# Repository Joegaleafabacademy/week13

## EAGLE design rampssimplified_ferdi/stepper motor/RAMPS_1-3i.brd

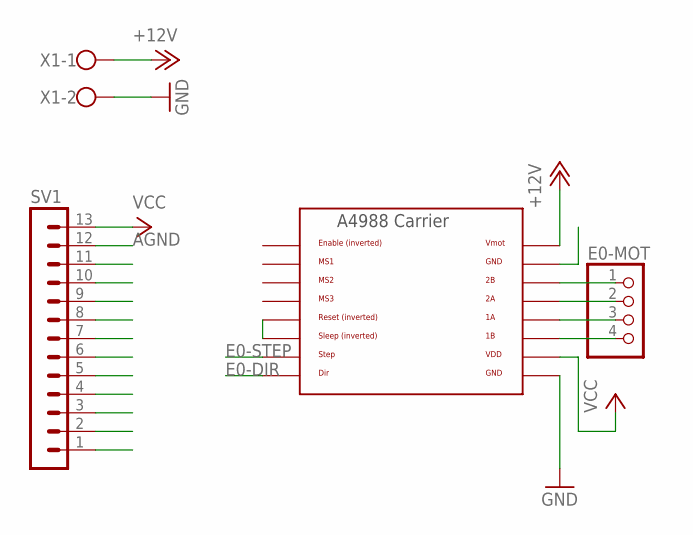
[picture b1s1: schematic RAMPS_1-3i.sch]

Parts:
E0-MOT: PINHD-1X4; 1X04
SV1: MA13-1
U$4: A4988BREAKOUT
X1: W237-102

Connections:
+12V: U$4.VMOT, X1.1
AGND: SV1.12, U$4.GND
E0-DIR: SV1.1, U$4.DIR
E0-STEP: SV1.2, U$4.STEP
GND: U$4.GND@0 (GND), X1.2
unnamed: E0-MOT.1, U$4.2B
unnamed: E0-MOT.2, U$4.2A
unnamed: U$4.RST, U$4.SLP (SLEEP)
unnamed: E0-MOT.3, U$4.1A
unnamed: E0-MOT.4, U$4.1B
VCC: SV1.13, U$4.VDD

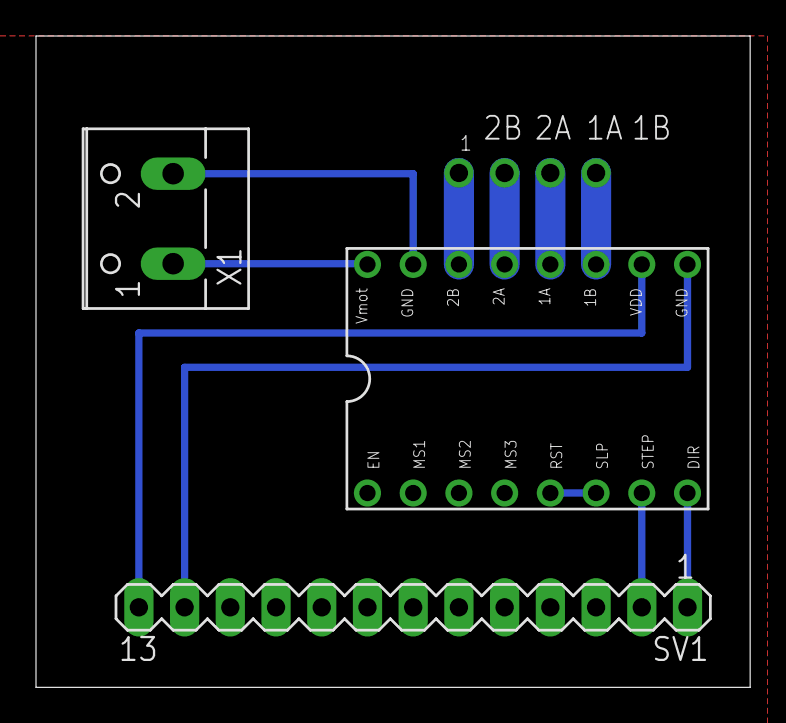
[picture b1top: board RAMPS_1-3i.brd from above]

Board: 2 copper layers, 39.7 x 36.2 mm, 4 parts (0 on the bottom side), 11 nets.

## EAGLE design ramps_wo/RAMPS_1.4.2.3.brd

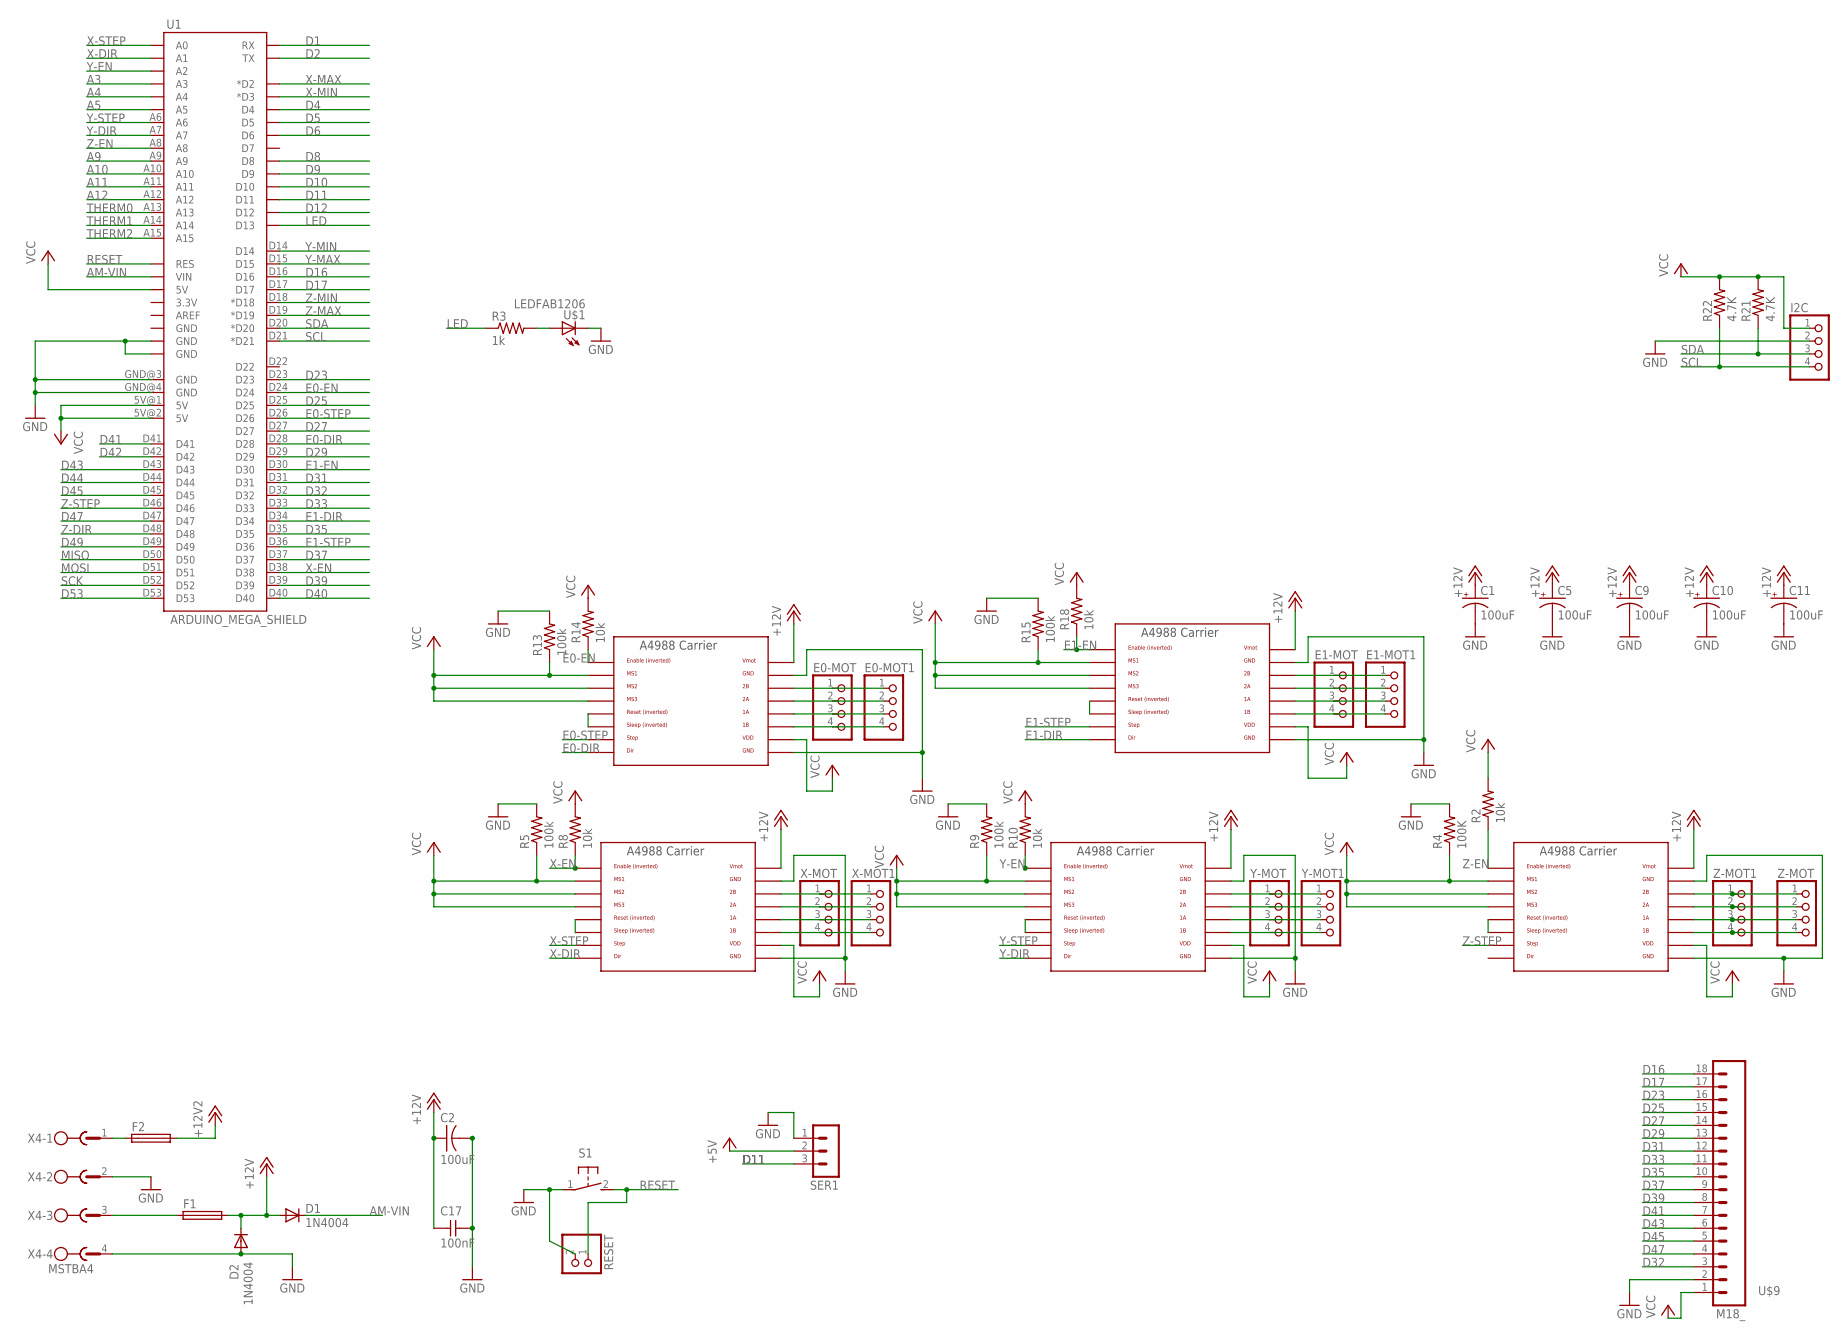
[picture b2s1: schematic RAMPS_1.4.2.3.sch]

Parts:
C1, C5, C9, C10, C11: 100uF; 153CLV-0605
C2: 100uF; C1206FAB
C17: 100nF; C1206FAB
D1, D2: 1N4004; DO41-10
E0-MOT, E0-MOT1, E1-MOT, E1-MOT1: PINHD-1X4; 1X04
F1, F2: FUSE_MCCQ-122
I2C: PINHD-1X4; 1X04
R2, R8, R10, R14, R18: 10k; R1206FAB
R3: 1k; R1206FAB
R4: 100K; R1206FAB
R5, R9, R13, R15: 100k; R1206FAB
R21, R22: 4.7K; R0805
RESET: PINHD-2
S1: 31-XX; B3F-31XX
SER1: 3PIN-HEADER
U1: ARDUINO_MEGA_SHIELD
U$1: LEDFAB1206; LED1206FAB
U$4, U$5, U$6, U$7, U$8: A4988BREAKOUT
U$9: M18_; 1X18
X4: MSTBA4
X-MOT, X-MOT1: PINHD-1X4; 1X04
Y-MOT, Y-MOT1: PINHD-1X4; 1X04
Z-MOT, Z-MOT1: PINHD-1X4; 1X04

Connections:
+5V: SER1.2
+12V: C1.+, C2.1, C5.+, C9.+, C10.+, C11.+, C17.1, D1.A, D2.C, F1.2-1 (2), F1.2-2 (2), U$4.VMOT, U$5.VMOT, U$6.VMOT, U$7.VMOT, U$8.VMOT
+12V2: F2.2-1 (2), F2.2-2 (2)
A3: U1.A3
A4: U1.A4
A5: U1.A5
A9: U1.A9
A10: U1.A10
A11: U1.A11
A12: U1.A12
AM-VIN: D1.C, U1.VIN
D1: U1.RX
D2: U1.TX
D4: U1.D4
D5: U1.D5
D6: U1.D6
D8: U1.D8
D9: U1.D9
D10: U1.D10
D11: SER1.3, U1.D11
D12: U1.D12
D16: U1.D16, U$9.18
D17: U1.D17, U$9.17
D23: U1.D23, U$9.16
D25: U1.D25, U$9.15
D27: U1.D27, U$9.14
D29: U1.D29, U$9.13
D31: U1.D31, U$9.12
D32: U1.D32, U$9.3
D33: U1.D33, U$9.11
D35: U1.D35, U$9.10
D37: U1.D37, U$9.9
D39: U1.D39, U$9.8
D40: U1.D40
D41: U1.D41, U$9.7
D42: U1.D42
D43: U1.D43, U$9.6
D44: U1.D44
D45: U1.D45, U$9.5
D47: U1.D47, U$9.4
D49: U1.D49
D53: U1.D53
E0-DIR: U1.D28, U$4.DIR
E0-EN: R14.1, U1.D24, U$4.EN
E0-STEP: U1.D26, U$4.STEP
E1-DIR: U1.D34, U$5.DIR
E1-EN: R18.1, U1.D30, U$5.EN
E1-STEP: U1.D36, U$5.STEP
GND: C1.-, C2.2, C5.-, C9.-, C10.-, C11.-, C17.2, D2.A, I2C.2, R4.2, R5.2, R9.2, R13.2, R15.2, RESET.2, S1.1, SER1.1, U1.GND@0 (GND), U1.GND@1 (GND), U1.GND@3 (GND), U1.GND@4 (GND), U$1.2 (C), U$4.GND, U$4.GND@0 (GND), U$5.GND, U$5.GND@0 (GND), U$6.GND, U$6.GND@0 (GND), U$7.GND, U$7.GND@0 (GND), U$8.GND, U$8.GND@0 (GND), U$9.2, X4.2, X4.4
LED: R3.1, U1.D13
MISO: U1.D50
MOSI: U1.D51
unnamed: E0-MOT.1, E0-MOT1.1, U$4.2B
unnamed: E0-MOT.2, E0-MOT1.2, U$4.2A
unnamed: U$4.RST, U$4.SLP (SLEEP)
unnamed: E0-MOT.3, E0-MOT1.3, U$4.1A
unnamed: E0-MOT.4, E0-MOT1.4, U$4.1B
unnamed: E1-MOT.1, E1-MOT1.1, U$5.2B
unnamed: E1-MOT.2, E1-MOT1.2, U$5.2A
unnamed: E1-MOT.3, E1-MOT1.3, U$5.1A
unnamed: E1-MOT.4, E1-MOT1.4, U$5.1B
unnamed: U$6.RST, U$6.SLP (SLEEP)
unnamed: U$6.2B, X-MOT.1, X-MOT1.1
unnamed: U$6.2A, X-MOT.2, X-MOT1.2
unnamed: U$7.RST, U$7.SLP (SLEEP)
unnamed: U$5.RST, U$5.SLP (SLEEP)
unnamed: U$6.1A, X-MOT.3, X-MOT1.3
unnamed: U$6.1B, X-MOT.4, X-MOT1.4
unnamed: U$7.2B, Y-MOT.1, Y-MOT1.1
unnamed: U$7.2A, Y-MOT.2, Y-MOT1.2
unnamed: U$7.1A, Y-MOT.3, Y-MOT1.3
unnamed: U$7.1B, Y-MOT.4, Y-MOT1.4
unnamed: U$8.RST, U$8.SLP (SLEEP)
unnamed: U$8.2B, Z-MOT.1, Z-MOT1.1
unnamed: U$8.2A, Z-MOT.2, Z-MOT1.2
unnamed: U$8.1A, Z-MOT.3, Z-MOT1.3
unnamed: U$8.1B, Z-MOT.4, Z-MOT1.4
unnamed: R3.2, U$1.1 (A)
unnamed: F2.1-1 (1), F2.1-2 (1), X4.1
unnamed: F1.1-1 (1), F1.1-2 (1), X4.3
RESET: RESET.1, S1.2 (S), U1.RES
SCK: U1.D52
SCL: I2C.4, R22.1, U1.D21 (*D21)
SDA: I2C.3, R21.1, U1.D20 (*D20)
THERM0: U1.A13
THERM1: U1.A14
THERM2: U1.A15
VCC: I2C.1, R2.2, R4.1, R5.1, R8.2, R9.1, R10.2, R13.1, R14.2, R15.1, R18.2, R21.2, R22.2, U1.5V@0 (5V), U1.5V@1 (5V), U1.5V@2 (5V), U$4.MS1, U$4.MS2, U$4.MS3, U$4.VDD, U$5.MS1, U$5.MS2, U$5.MS3, U$5.VDD, U$6.MS1, U$6.MS2, U$6.MS3, U$6.VDD, U$7.MS1, U$7.MS2, U$7.MS3, U$7.VDD, U$8.MS1, U$8.MS2, U$8.MS3, U$8.VDD, U$9.1
X-DIR: U1.A1, U$6.DIR
X-EN: R8.1, U1.D38, U$6.EN
X-MAX: U1.D2 (*D2)
X-MIN: U1.D3 (*D3)
X-STEP: U1.A0, U$6.STEP
Y-DIR: U1.A7, U$7.DIR
Y-EN: R10.1, U1.A2, U$7.EN
Y-MAX: U1.D15
Y-MIN: U1.D14
Y-STEP: U1.A6, U$7.STEP
Z-DIR: U1.D48
Z-EN: R2.1, U1.A8, U$8.EN
Z-MAX: U1.D19 (*D19)
Z-MIN: U1.D18 (*D18)
Z-STEP: U1.D46, U$8.STEP

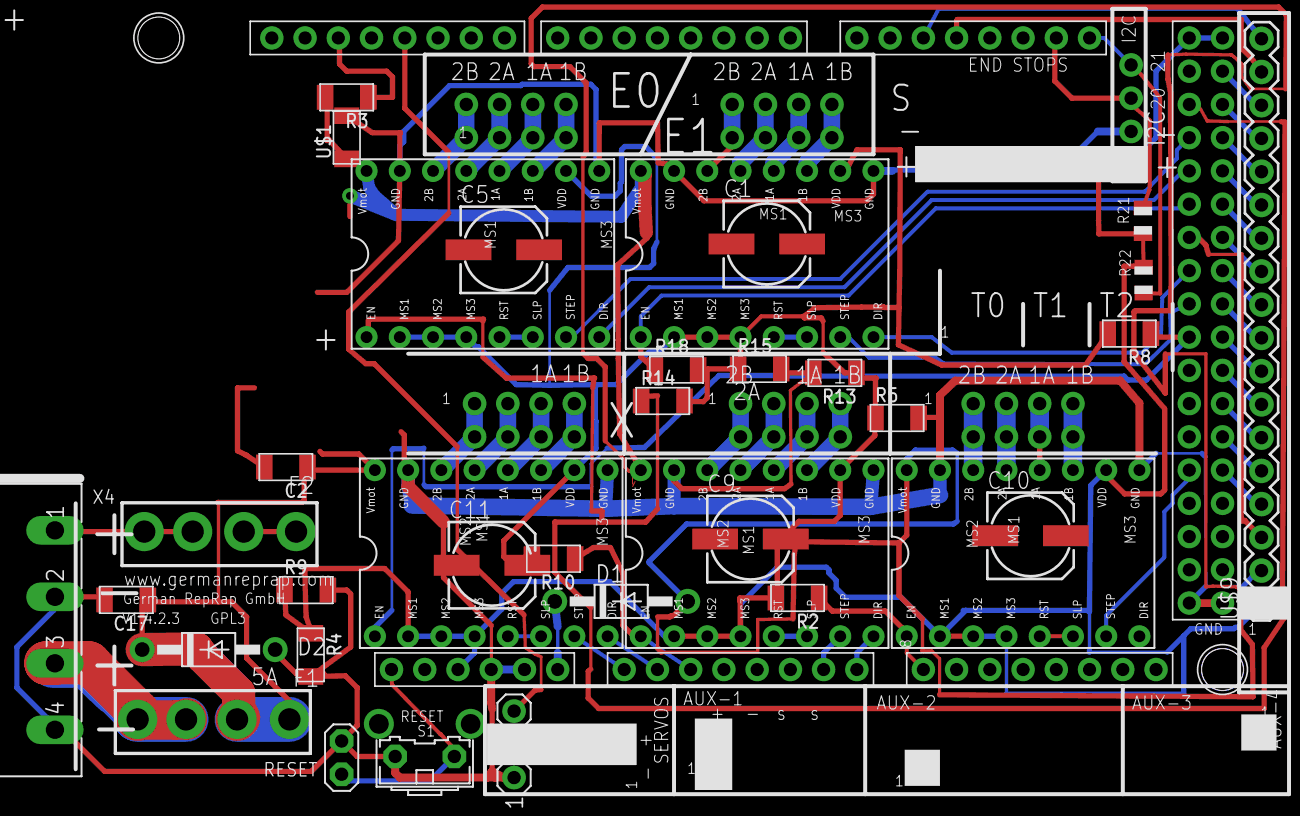
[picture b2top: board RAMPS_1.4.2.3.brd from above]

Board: 2 copper layers, 47 parts (0 on the bottom side), 68 nets.

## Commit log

2016-06-05 output devices

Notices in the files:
RAMPS_1.4.2.3.sch:
Copyright 2011 Johnny Russell
GPL v3
ramps_wo/RAMPS_1.4.2.3.brd:
GPL3
Copyright 2011 Johnny Russell - UltiMachine
